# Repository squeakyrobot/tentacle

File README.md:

# tentacle
Modular robotic tentacle

TODO: On the project webpage add a simple calculator to help with the tentacle setup that allows the user to
easily configure their tentacle. Also add the maths in this document

## BOM

 * Internal Bearings - [F683ZZ](https://www.amazon.com/gp/product/B07Z3DRZX9)
 * Pulley Bearings - [6700-2RS](https://www.amazon.com/gp/product/B082PR3DFZ)

## Motor Options

## 28BYJ-48
I modified these motors to be bipolar, See [this article](https://ardufocus.com/howto/28byj-48-bipolar-hw-mod/)

## TODO:

- Add NEMA-11 support
- Add NEMA-14 support
- Test different configurations
    - Spine size
        - 4mm OD, 3mm ID
        - 4mm OD, 2mm ID
        - 6mm OD, 3mm ID
    - Cable materials

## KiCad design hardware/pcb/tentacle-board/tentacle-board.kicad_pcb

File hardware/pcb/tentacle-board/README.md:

# Tentacle Controller PCB

TODO: Add more details about the board

## Pinout

Both motors share microstep configuration pins and the enable pin.

### Microstep Configuration

| **DRV8825 Pin** 	| **RP2040 Pin** 	|
|-----------------	|----------------	|
| MODE 0           	| GPIO3          	|
| MODE 1           	| GPIO2          	|
| MODE 2          	| GPIO1          	|

### Motor A

| **DRV8825 Pin** 	| **RP2040 Pin** 	|
|-----------------	|----------------	|
| DIR             	| GPIO6          	|
| STEP            	| GPIO4          	|
| ENABLE          	| GPIO5          	|
| SLEEP           	| GPIO8          	|
| RESET           	| GPIO9          	|
| HOME            	| GPIO0          	|
| FAULT           	| GPIO7          	|

### Motor B

| **DRV8825 Pin** 	| **RP2040 Pin** 	|
|-----------------	|----------------	|
| DIR             	| GPIO12          	|
| STEP            	| GPIO11          	|
| ENABLE          	| GPIO5          	|
| SLEEP           	| GPIO14          	|
| RESET           	| GPIO15          	|
| HOME            	| GPIO10          	|
| FAULT           	| GPIO13          	|

### Debug Connector

| **Connector Pin** | **RP2040 Pin** |
|-----------------	|----------------|
| 1             	| SWCLK          |
| 2            	    | GND          	 |
| 3           	    | SWD          	 |

### UART Connector

| **Connector Pin** | **RP2040 Pin**    | **Pin Functions** |
|-----------------	|----------------   |----------------   |
| 1             	| GPIO17            | UART0 RX          |
| 2            	    | GND          	    |                   |
| 3           	    | GPIO16            | UART0 TX          |

### CTRL Connector

| **Connector Pin** | **RP2040 Pin**    | **Pin Functions**     |
|-----------------	|----------------   |----------------       |
| 1             	| GND               |                       |
| 2            	    | RUN      	        | Reset when driven low |
| 3           	    | GPIO19            |                       |
| 4           	    | GPIO20            | UART1 TX, I2C0 SDA    |
| 5           	    | GPIO21            | UART1 RX, I2C0 SCL    |

### AUX1 Connector

| **Connector Pin** | **RP2040 Pin**    | **Pin Functions**     |
|-----------------	|----------------   |----------------       |
| 1             	| GND               |                       |
| 2            	    | GPIO22      	    |                       |
| 3           	    | GPIO23            |                       |
| 4           	    | GPIO24            |                       |
| 5           	    | GPIO25            |                       |

### AUX2 Connector

| **Connector Pin** | **RP2040 Pin**    | **Pin Functions**     |
|-----------------	|----------------   |----------------       |
| 1             	| GND               |                       |
| 2            	    | GPIO26      	    | ADC0                  |
| 3           	    | GPIO27            | ADC1                  |
| 4           	    | GPIO28            | ADC2                  |
| 5           	    | GPIO29            | ADC3                  |

### Motor Connectors

All motor connectors map to the same pins of their corresponding DRV8825 modules 

| **Connector Pin** | **DRV8825 Pin**   |
|-----------------	|----------------	|
| 1             	| B2          	    |
| 2            	    | B1          	    |
| 3          	    | A1          	    |
| 4           	    | A2          	    |

## Revision History

### v1.0

 * Initial Release

### v1.1

 * **NOT COMPLETE**
 * Fix issue with missing silkscreen items

## TODO:

 * Investigate alternative motor connectors
    - Change to JST-PH 2mm
 * Investigate alternative power connector
 * Switch interface connectors to right angle
 * Switch to a shared SLEEP and individual ENABLE
 * Add software configurable VREF, perhaps have the pot be the max
 * Make CTRL & AUX connectors 90 degrees

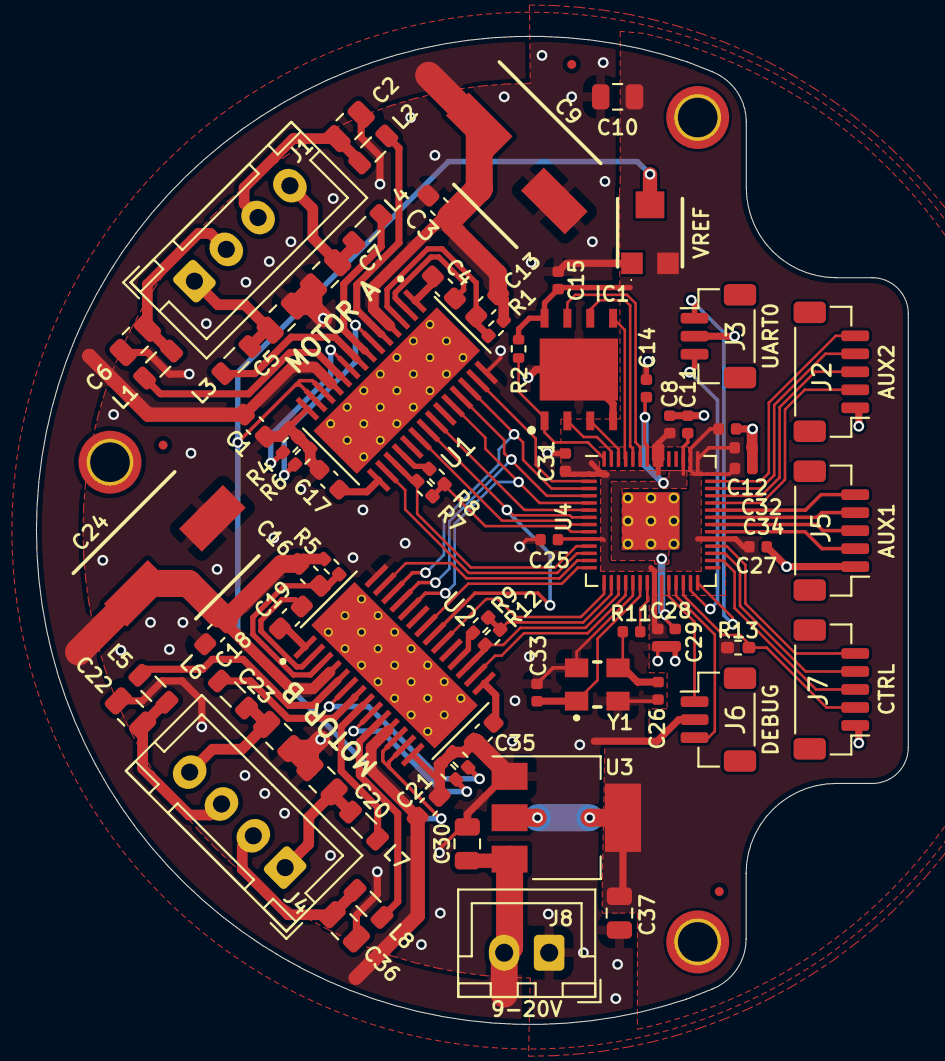
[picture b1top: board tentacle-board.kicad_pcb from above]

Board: 2 copper layers, 48.4 x 54.9 mm, 79 parts (0 on the bottom side), 76 nets.

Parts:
C1, C3, C13, C16, C18, C21: 0.1uf; C_0603_1608Metric_Pad1.08x0.95mm_HandSolder
C2, C5, C6, C7, C20, C22, C23, C36: 1nF; C_0805_2012Metric
C4, C19: 10nF; C_0603_1608Metric_Pad1.08x0.95mm_HandSolder
C8, C14, C15, C25, C27, C28, C29, C31, C32, C34: 100nF; C_0402_1005Metric
C9, C24: 100uF; CAPAE660X800N
C10, C30, C37: 10uF; C_0805_2012Metric
C11, C12: 1uF; C_0402_1005Metric
C17, C35: 0.47uF; C_0603_1608Metric
C26, C33: 30pF; C_0402_1005Metric
FID1, FID2, FID3: Fiducial; Fiducial_0.5mm_Mask1mm
H1, H2, H3: MountingHole; MountingHole_2.2mm_M2_ISO7380_Pad_TopBottom
IC1: W25Q32JVZPIQ; SON127P600X500X80-9N-D
J1, J4: Motor; JST_XH_B4B-XH-A_1x04_P2.50mm_Vertical
J2: AUX2; JST_SH_BM05B-SRSS-TB_1x05-1MP_P1.00mm_Vertical
J3: UART0; JST_SH_BM03B-SRSS-TB_1x03-1MP_P1.00mm_Vertical
J5: AUX1; JST_SH_BM05B-SRSS-TB_1x05-1MP_P1.00mm_Vertical
J6: DEBUG; JST_SH_BM03B-SRSS-TB_1x03-1MP_P1.00mm_Vertical
J7: CTRL; JST_SH_BM05B-SRSS-TB_1x05-1MP_P1.00mm_Vertical
J8: Conn_01x02; JST_XH_B2B-XH-A_1x02_P2.50mm_Vertical
L1, L2, L3, L4, L5, L6, L7, L8: L_Ferrite; L_0805_2012Metric
R1, R5: 1M; R_0402_1005Metric_Pad0.72x0.64mm_HandSolder
R2: 10k; R_0402_1005Metric
R3, R4, R6, R10: 0.1; R_0402_1005Metric_Pad0.72x0.64mm_HandSolder
R7, R12: 10k; R_0402_1005Metric_Pad0.72x0.64mm_HandSolder
R8, R9, R13: 1.5k; R_0402_1005Metric_Pad0.72x0.64mm_HandSolder
R11: 1k; C_0402_1005Metric
U1, U2: DRV8825PWP; IC_TPS61196PWPRQ1
U3: NCP1117-3.3_SOT223; SOT-223-3_TabPin2
U4: RP2040; RP2040-QFN-56
VR1: TC33X-2-103E; TC33X2503E
Y1: ABM8-12.000MHZ-20-B1U-T; ABM810000MHZ12D2W

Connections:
+1V1: C11.1, C14.1, C29.1, U4.23 (DVDD), U4.45 (VREG_VOUT), U4.50 (DVDD)
+3V3: C8.1, C10.1, C12.1, C15.1, C25.1, C27.1, C28.1, C31.1, C32.1, C34.1, C37.1, IC1.8 (VCC), R2.1, R13.2, U3.2 (VO), U4.1 (IOVDD), U4.10 (IOVDD), U4.22 (IOVDD), U4.33 (IOVDD), U4.42 (IOVDD), U4.43 (ADC_AVDD), U4.44 (VREG_IN), U4.48 (USB_VDD), U4.49 (IOVDD), VR1.3 (CW)
/GPIO0: U1.27 (NHOME), U4.2 (GPIO0)
/GPIO1: U1.26 (MODE2), U2.26 (MODE2), U4.3 (GPIO1)
/GPIO2: U1.25 (MODE1), U2.25 (MODE1), U4.4 (GPIO2)
/GPIO3: U1.24 (MODE0), U2.24 (MODE0), U4.5 (GPIO3)
/GPIO4: U1.22 (STEP), U4.6 (GPIO4)
/GPIO5: U1.21 (NENBL), U2.21 (NENBL), U4.7 (GPIO5)
/GPIO6: U1.20 (DIR), U4.8 (GPIO6)
/GPIO7: R7.1, R8.2, U4.9 (GPIO7)
/GPIO8: R7.2, U1.17 (NSLEEP), U4.11 (GPIO8)
/GPIO9: U1.16 (~NRESET), U4.12 (GPIO9)
/GPIO10: U2.27 (NHOME), U4.13 (GPIO10)
/GPIO11: U2.22 (STEP), U4.14 (GPIO11)
/GPIO12: U2.20 (DIR), U4.15 (GPIO12)
/GPIO13: R9.2, R12.1, U4.16 (GPIO13)
/GPIO14: R12.2, U2.17 (NSLEEP), U4.17 (GPIO14)
/GPIO15: U2.16 (~NRESET), U4.18 (GPIO15)
/GPIO16: J3.3, U4.27 (GPIO16)
/GPIO17: J3.1, U4.28 (GPIO17)
/GPIO19: J7.3, U4.30 (GPIO19)
/GPIO20: J7.4, U4.31 (GPIO20)
/GPIO21: J7.5, U4.32 (GPIO21)
/GPIO22: J5.2, U4.34 (GPIO22)
/GPIO23: J5.3, U4.35 (GPIO23)
/GPIO24: J5.4, U4.36 (GPIO24)
/GPIO25: J5.5, U4.37 (GPIO25)
/GPIO26_ADC0: J2.2, U4.38 (GPIO26_ADC0)
/GPIO27_ADC1: J2.3, U4.39 (GPIO27_ADC1)
/GPIO28_ADC2: J2.4, U4.40 (GPIO28_ADC2)
/GPIO29_ADC3: J2.5, U4.41 (GPIO29_ADC3)
/Motor Driver A/A1: C2.1, J1.3, L2.2
/Motor Driver A/A2: C7.1, J1.4, L4.2
/Motor Driver A/B1: C6.1, J1.2, L1.2
/Motor Driver A/B2: C5.1, J1.1, L3.2
/Motor Driver A/VREF: U1.12 (AVREF), U1.13 (BVREF), U2.12 (AVREF), U2.13 (BVREF), VR1.2 (WIPER)
/Motor Driver B/A1: C22.1, J4.3, L5.2
/Motor Driver B/A2: C23.1, J4.4, L6.2
/Motor Driver B/B1: C36.1, J4.2, L8.2
/Motor Driver B/B2: C20.1, J4.1, L7.2
/QSPI_SCLK: IC1.6 (CLK), U4.52 (QSPI_SCLK)
/QSPI_SD0: IC1.5 (DI_(IO0)), U4.53 (QSPI_SD0)
/QSPI_SD1: IC1.2 (DO_(IO1)), U4.55 (QSPI_SD1)
/QSPI_SD2: IC1.3 (~WP_(IO2)), U4.54 (QSPI_SD2)
/QSPI_SD3: IC1.7 (~RESET_(IO3)), U4.51 (QSPI_SD3)
/QSPI_SS: IC1.1 (~CS), R2.2, U4.56 (QSPI_SS)
/RUN: J7.2, R13.1, U4.26 (RUN)
/SWCLK: J6.1, U4.24 (SWCLK)
/SWD: J6.3, U4.25 (SWD)
/XIN: C33.1, U4.20 (XIN), Y1.1 (X1)
/XOUT: R11.1, U4.21 (XOUT)
GND: C1.2, C2.2, C3.2, C5.2, C6.2, C7.2, C8.2, C9.2, C10.2, C11.2, C12.2, C14.2, C15.2, C17.2, C18.2, C20.2, C21.2, C22.2, C23.2, C24.2, C25.2, C26.2, C27.2, C28.2, C29.2, C30.2, C31.2, C32.2, C33.2, C34.2, C35.2, C36.2, C37.2, IC1.4 (GND), IC1.9 (EP), J2.1, J3.2, J5.1, J6.2, J7.1, J8.1, R3.2, R4.2, R6.2, R10.2, U1.14 (GND), U1.28 (GND__1), U2.14 (GND), U2.28 (GND__1), U3.1 (GND), U4.19 (TESTEN), U4.57 (GND), VR1.1 (CCW), Y1.2 (GND_1), Y1.4 (GND_2)
unnamed: L2.1, U1.5 (AOUT1)
unnamed: L4.1, U1.7 (AOUT2)
unnamed: L1.1, U1.10 (BOUT1)
unnamed: L3.1, U1.8 (BOUT2)
unnamed: C4.1, U1.1 (CP1)
unnamed: C4.2, U1.2 (CP2)
unnamed: R6.1, U1.6 (ISENA)
unnamed: R4.1, U1.9 (ISENB)
unnamed: R8.1, U1.18 (NFAULT)
unnamed: C17.1, U1.15 (V3P3OUT)
unnamed: C13.1, R1.2, U1.3 (VCP)
unnamed: L5.1, U2.5 (AOUT1)
unnamed: L6.1, U2.7 (AOUT2)
unnamed: L8.1, U2.10 (BOUT1)
unnamed: L7.1, U2.8 (BOUT2)
unnamed: C19.1, U2.1 (CP1)
unnamed: C19.2, U2.2 (CP2)
unnamed: R10.1, U2.6 (ISENA)
unnamed: R3.1, U2.9 (ISENB)
unnamed: R9.1, U2.18 (NFAULT)
unnamed: C35.1, U2.15 (V3P3OUT)
unnamed: C16.1, R5.2, U2.3 (VCP)
unnamed: C26.1, R11.2, Y1.3 (X2)
VDC: C1.1, C3.1, C9.1, C13.2, C16.2, C18.1, C21.1, C24.1, C30.1, J8.2, R1.1, R5.1, U1.4 (VMA), U1.11 (VMB), U2.4 (VMA), U2.11 (VMB), U3.3 (VI)

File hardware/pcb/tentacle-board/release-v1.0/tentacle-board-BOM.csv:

Id,Designator,Footprint,Quantity,Designation,LCSC Part Number
1,"C37,C30,C10",C_0805_2012Metric,3,10uF,C15850
2,"C12,C11",C_0402_1005Metric,2,1uF,C107372
3,"C25,C15,C8,C27,C28,C29,C31,C32,C14,C34",C_0402_1005Metric,10,100nF,C60474
4,U3,SOT-223-3_TabPin2,1,NCP1117-3.3_SOT223,C2902118
5,"C26,C33",C_0402_1005Metric,2,30pF,C107004
6,U4,RP2040-QFN-56,1,RP2040,C2040
7,R11,C_0402_1005Metric,1,1k,C11702
8,Y1,ABM810000MHZ12D2W,1,ABM8-12.000MHZ-20-B1U-T,C133334
9,VR1,TC33X2503E,1,TC33X-2-103E,C719176
10,"J7,J2,J5",JST_SH_BM05B-SRSS-TB_1x05-1MP_P1.00mm_Vertical,1,JST_SH_BM05B,C160391
11,"L7,L6,L2,L8,L5,L1,L3,L4",L_0805_2012Metric,8,L_Ferrite,C369519
12,"R6,R3,R4,R10",R_0402_1005Metric_Pad0.72x0.64mm_HandSolder,4,0.1ohms,C3013344
13,"R5,R1",R_0402_1005Metric_Pad0.72x0.64mm_HandSolder,2,1M,C138033
14,"C20,C2,C22,C23,C5,C6,C36,C7",C_0805_2012Metric,8,1nF,C51210
15,"C35,C17",C_0603_1608Metric,2,0.47uF,C577418
17,"J4,J1",JST_XH_B4B-XH-A_1x04_P2.50mm_Vertical,2,Motor,C37815
18,"J6,J3",JST_SH_BM03B-SRSS-TB_1x03-1MP_P1.00mm_Vertical,1,BM03B-SRSS,C160389
19,"C4,C19",C_0603_1608Metric_Pad1.08x0.95mm_HandSolder,2,10nF,C100042
20,"C3,C16,C1,C18,C21,C13",C_0603_1608Metric_Pad1.08x0.95mm_HandSolder,6,0.1uf,C3011705
21,"R12,R7,R2",R_0402,2,10k,C60490
23,"C9,C24",CAPAE660X800N,2,100uF,C250945
24,"U1,U2",IC_TPS61196PWPRQ1,2,DRV8825PWP,C81582
25,IC1,SON127P600X500X80-9N-D,1,W25Q32JVZPIQ,C571260
26,"R9,R8,R13",R_0402_1005Metric_Pad0.72x0.64mm_HandSolder,3,1.5k,C114759
29,J8,JST_XH_B2B-XH-A_1x02_P2.50mm_Vertical,1,Power,C442299

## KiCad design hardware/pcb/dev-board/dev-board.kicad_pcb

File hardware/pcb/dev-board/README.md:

# Development Board

TODO: Add more details about the board

## Pinout

### Microstep Configuration

Both motors share microstep configuration pins

| **DRV8825 Pin** 	| **Pico Pin** 	|
|-----------------	|----------------	|
| MODE 0           	| GPIO2          	|
| MODE 1           	| GPIO3          	|
| MODE 2          	| GPIO4          	|

### Motor 1

| **DRV8825 Pin** 	| **Pico Pin** 	    |
|-----------------	|----------------   |
| DIR             	| GPIO7          	|
| STEP            	| GPIO6          	|
| ENABLE          	| GND          	    |
| SLEEP           	| GPIO8          	|
| RESET           	| GND          	    |
| FAULT           	| GND          	    |

### Motor 2

| **DRV8825 Pin** 	| **Pico Pin** 	    |
|-----------------	|----------------   |
| DIR             	| GPIO10          	|
| STEP            	| GPIO9          	|
| ENABLE          	| GND          	    |
| SLEEP           	| GPIO8          	|
| RESET           	| GND          	    |
| FAULT           	| GND          	    |

### Motor 3

| **DRV8825 Pin** 	| **Pico Pin** 	    |
|-----------------	|----------------   |
| DIR             	| GPIO13          	|
| STEP            	| GPIO12          	|
| ENABLE          	| GND          	    |
| SLEEP           	| GPIO11          	|
| RESET           	| GND          	    |
| FAULT           	| GND          	    |

### Motor 4

| **DRV8825 Pin** 	| **Pico Pin** 	    |
|-----------------	|----------------   |
| DIR             	| GPIO16          	|
| STEP            	| GPIO15          	|
| ENABLE          	| GND          	    |
| SLEEP           	| GPIO14          	|
| RESET           	| GND          	    |
| FAULT           	| GND          	    |

### Motor Connectors

All motor connectors map to the same pins of their corresponding DRV8825 modules 

| **Connector Pin** | **DRV8825 Pin**   |
|-----------------	|----------------	|
| 1             	| B2          	    |
| 2            	    | B1          	    |
| 3          	    | A1          	    |
| 4           	    | A2          	    |

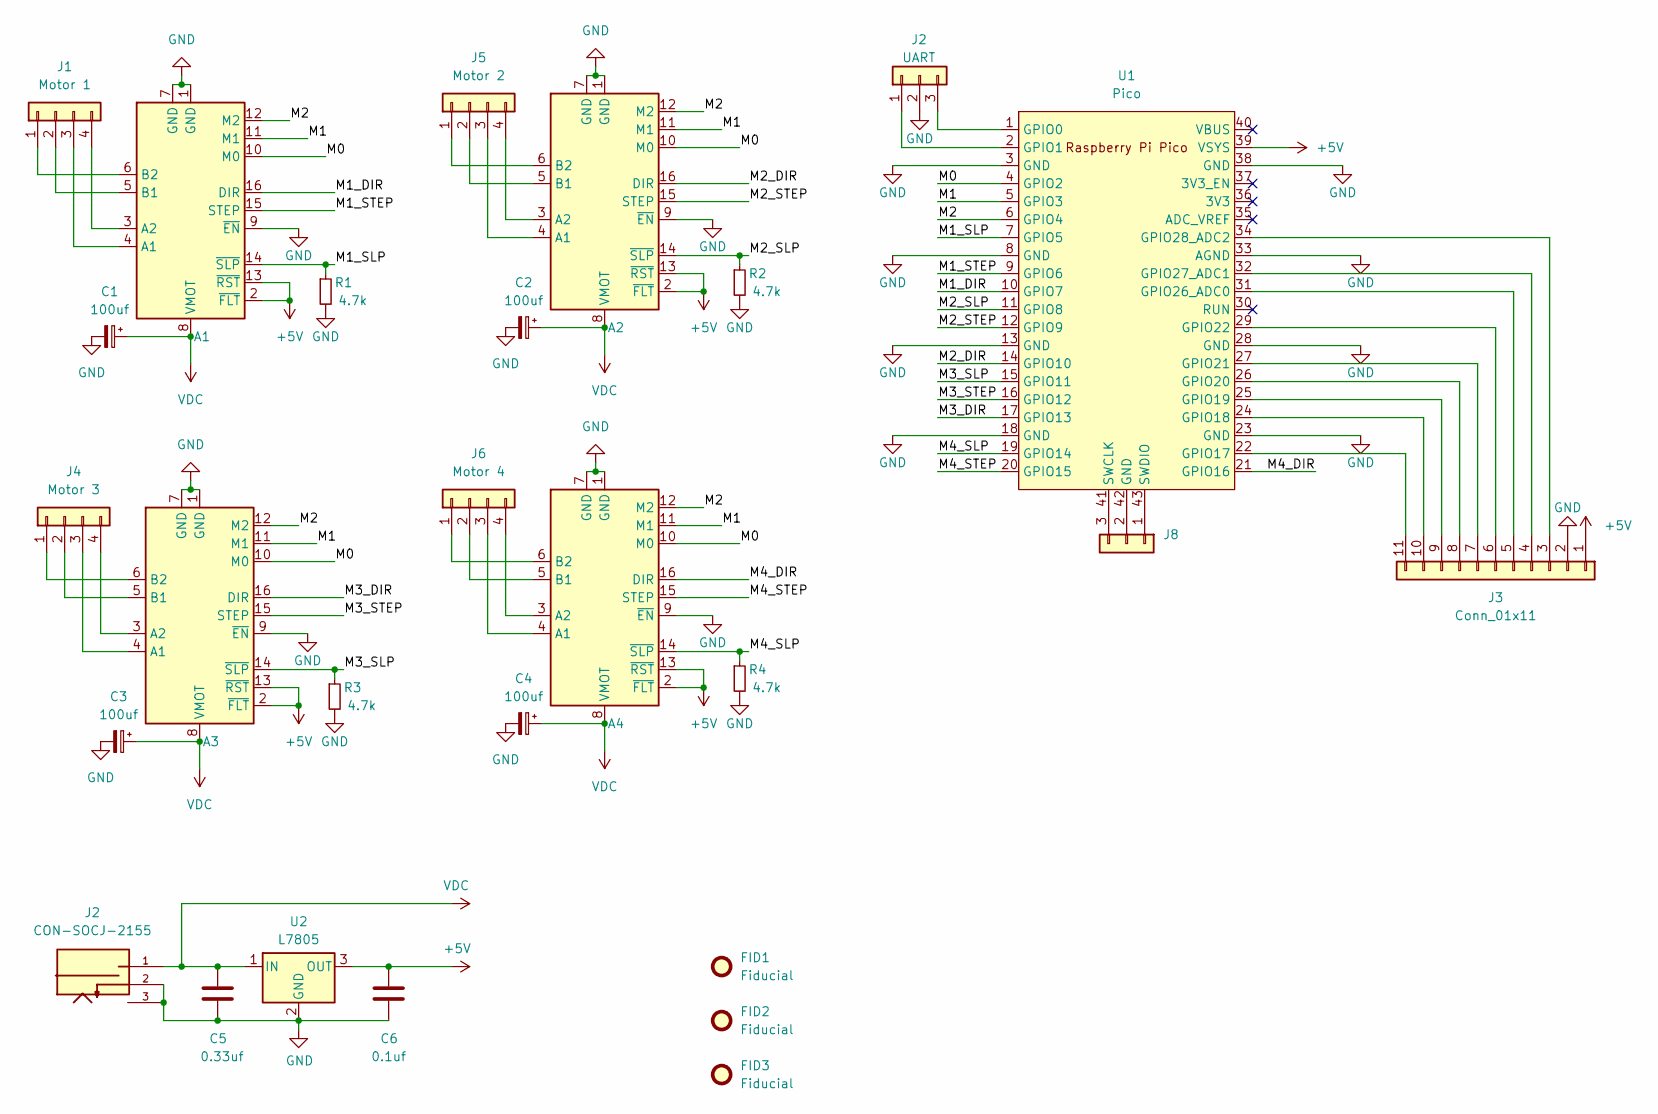
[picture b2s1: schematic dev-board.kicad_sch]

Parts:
A1, A2, A3, A4: Pololu_Breakout_DRV8825; Pololu_Breakout-16_15.2x20.3mm
C1, C2, C3, C4: 100uf; CP_Radial_D6.3mm_P2.50mm
C5: 0.33uf; C_0805_2012Metric_Pad1.18x1.45mm_HandSolder; Mfg # C0805C224K1RACTU; Mouser # 80-C0805C224K1R
C6: 0.1uf; C_0805_2012Metric_Pad1.18x1.45mm_HandSolder; Mfr # KGM21NR71H104KT; Mouser # 581-KGM21NR71H104KT
FID1, FID2, FID3: Fiducial; Fiducial_1mm_Mask2mm
J1: Motor 1; JST_XH_B4B-XH-A_1x04_P2.50mm_Vertical
J2: CON-SOCJ-2155; GRAVITECH_CON-SOCJ-2155; PARTREV NA
J3: Conn_01x11; PinHeader_1x11_P2.54mm_Vertical
J4: Motor 3; JST_XH_B4B-XH-A_1x04_P2.50mm_Vertical
J5: Motor 2; JST_XH_B4B-XH-A_1x04_P2.50mm_Vertical
J6: Motor 4; JST_XH_B4B-XH-A_1x04_P2.50mm_Vertical
J8: Conn_01x03; JST_XH_B3B-XH-A_1x03_P2.50mm_Vertical
R1, R2, R3, R4: 4.7k; R_0805_2012Metric_Pad1.20x1.40mm_HandSolder; Mfg # ERJ-HP6D4701V; Mouser # 667-ERJ-HP6D4701V
U1: Pico; RPi_Pico_SMD_TH
U2: L7805; TO-220-3_Vertical; Mfg # LM7805CT/NOPB

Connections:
+5V: A1.2 (~FLT), A1.13 (~RST), A2.2 (~FLT), A2.13 (~RST), A3.2 (~FLT), A3.13 (~RST), A4.2 (~FLT), A4.13 (~RST), C6.1, J3.1, U1.39 (VSYS), U2.3 (OUT)
/M0: A1.10 (M0), A2.10 (M0), A3.10 (M0), A4.10 (M0), U1.4 (GPIO2)
/M1: A1.11 (M1), A2.11 (M1), A3.11 (M1), A4.11 (M1), U1.5 (GPIO3)
/M1_DIR: A1.16 (DIR), U1.10 (GPIO7)
/M1_SLP: A1.14 (~SLP), R1.1, U1.7 (GPIO5)
/M1_STEP: A1.15 (STEP), U1.9 (GPIO6)
/M2: A1.12 (M2), A2.12 (M2), A3.12 (M2), A4.12 (M2), U1.6 (GPIO4)
/M2_DIR: A2.16 (DIR), U1.14 (GPIO10)
/M2_SLP: A2.14 (~SLP), R2.1, U1.11 (GPIO8)
/M2_STEP: A2.15 (STEP), U1.12 (GPIO9)
/M3_DIR: A3.16 (DIR), U1.17 (GPIO13)
/M3_SLP: A3.14 (~SLP), R3.1, U1.15 (GPIO11)
/M3_STEP: A3.15 (STEP), U1.16 (GPIO12)
/M4_DIR: A4.16 (DIR), U1.21 (GPIO16)
/M4_SLP: A4.14 (~SLP), R4.1, U1.19 (GPIO14)
/M4_STEP: A4.15 (STEP), U1.20 (GPIO15)
unnamed: A1.4 (A1), J1.3
unnamed: A1.3 (A2), J1.4
unnamed: A1.5 (B1), J1.2
unnamed: A1.6 (B2), J1.1
unnamed: A2.4 (A1), J5.3
unnamed: A2.3 (A2), J5.4
unnamed: A2.5 (B1), J5.2
unnamed: A2.6 (B2), J5.1
unnamed: A3.4 (A1), J4.3
unnamed: A3.3 (A2), J4.4
unnamed: A3.5 (B1), J4.2
unnamed: A3.6 (B2), J4.1
unnamed: A4.4 (A1), J6.3
unnamed: A4.3 (A2), J6.4
unnamed: A4.5 (B1), J6.2
unnamed: A4.6 (B2), J6.1
unnamed: J3.3, U1.34 (GPIO28_ADC2)
unnamed: J3.4, U1.32 (GPIO27_ADC1)
unnamed: J3.5, U1.31 (GPIO26_ADC0)
unnamed: J3.6, U1.29 (GPIO22)
unnamed: J3.7, U1.27 (GPIO21)
unnamed: J3.8, U1.26 (GPIO20)
unnamed: J3.9, U1.25 (GPIO19)
unnamed: J3.10, U1.24 (GPIO18)
unnamed: J3.11, U1.22 (GPIO17)
unnamed: J8.1, U1.43 (SWDIO)
unnamed: J8.2, U1.42 (GND)
unnamed: J8.3, U1.41 (SWCLK)

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
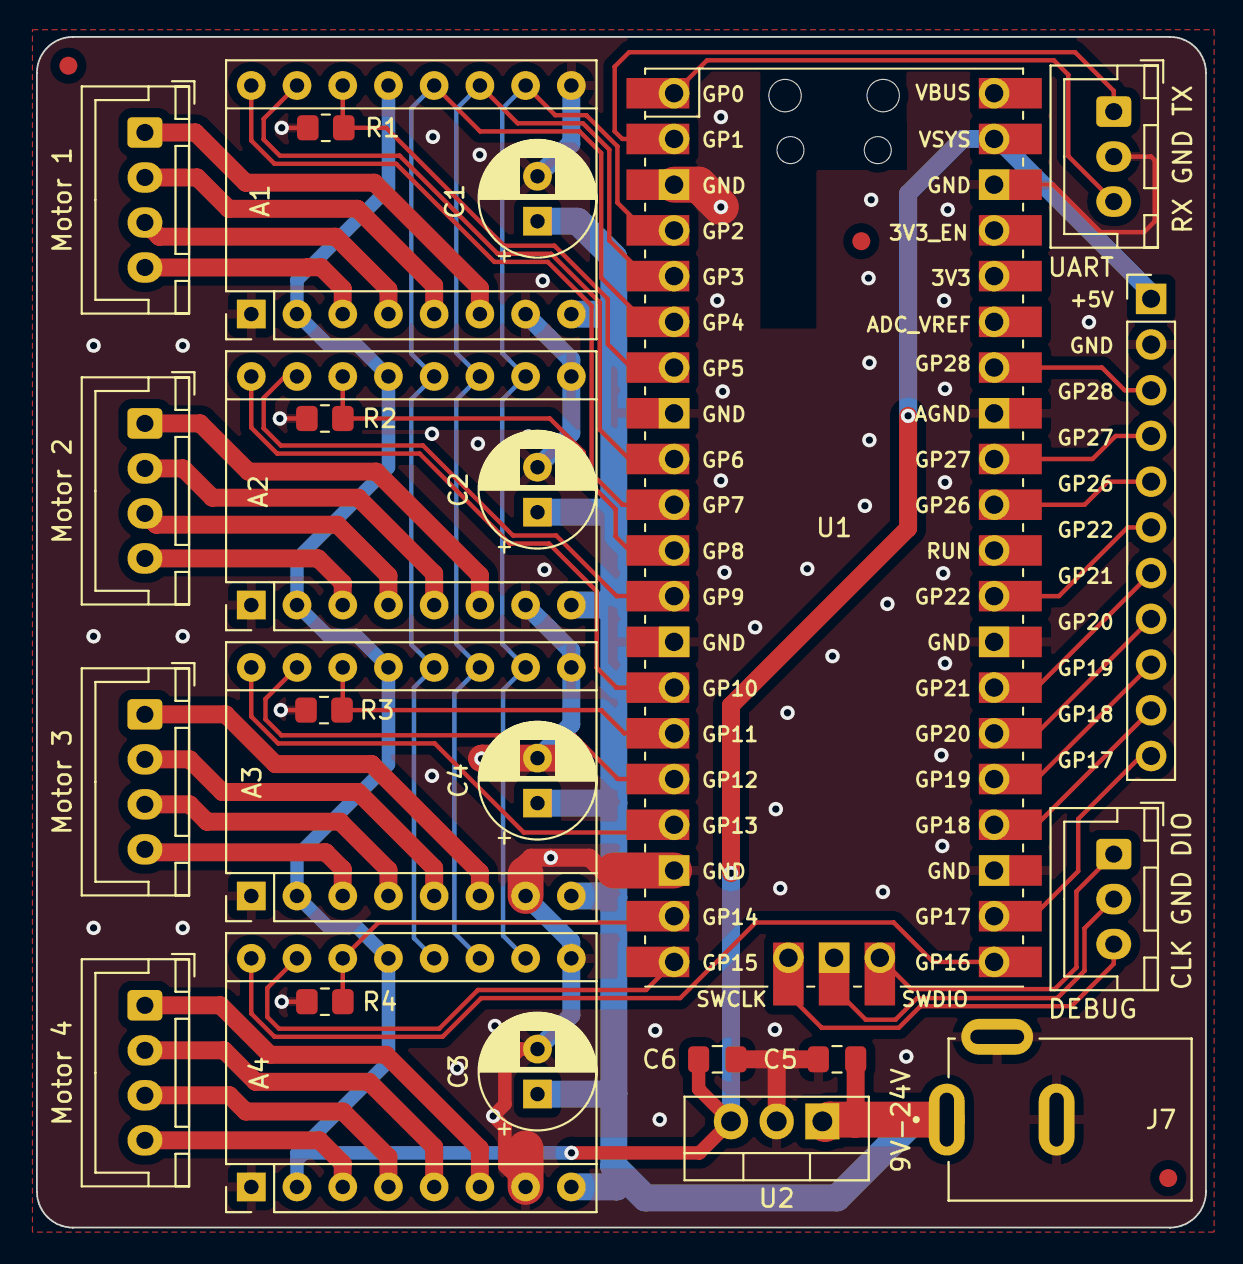
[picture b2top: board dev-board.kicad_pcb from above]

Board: 2 copper layers, 64.9 x 66.2 mm, 27 parts (0 on the bottom side), 48 nets.

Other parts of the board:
J7: CON-SOCJ-2155; GRAVITECH_CON-SOCJ-2155

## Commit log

2023-09-12 Added current stl files, and a project stub for the firmware
2023-09-12 Recreated stub pico project using https://github.com/raspberrypi/pico-project-generator
2023-09-13 Got the basic stepper driver tests done for DRV8830 and TMC2209
2023-09-13 Created the base motor driver interface and a timer based implementation
2023-09-13 Small refactor & reformatting
2023-09-14 Updated to use steps instead of time for stop calculations. Changed config to have maxRPM. Added rotateSteps.
2023-09-14 Moved most of the rotate functionality to the base class
2023-09-14 Added stub for pio driver, no implementation
2023-09-15 Added the interface and stubs for the tentacle controller
2023-09-15 Added gitkeeps to retain directory structure
2023-09-15 Added some, not much, of the tentacle controller implementation
2023-09-16 Added a step counter to the motor driver
2023-09-22 Added bearings to the motor base and did multiple experiments to get it functioning correctly
2023-09-26 Updated CAD & some basic testing
2023-10-13 Updated readme with some todos
2023-10-15 Modified the vertebrae to have a square semi-spherical joint to prevent twiasting and allow for more deterministic positioning
2023-10-17 Added custom PCB to use as a development board
2023-10-17 Finished dev board PCB
2023-10-17 Added stub PCB for the tentacle board based on the RP2049 minimal example
2023-10-18 Added stepper drivers to the tentacle controller PCB
2023-10-19 Worked on the motor power system and stepper driver BOM
2023-10-20 Added the MCU and supporting components and wired them up
2023-10-20 Updated flash to a smaller package, moved in the MCU to make some more room
2023-10-21 Updated references and formatted silkscreen layer
2023-10-23 Added aux plugs and updated the edge cuts
2023-10-24 Finished component & trace layout
2023-10-25 Finished v1 and created manufacturing outputs
2023-10-25 Added some images of the assembled dev-board
2023-11-03 Updated the firmware readme with pinout of the dev board and controller board
2023-11-03 Updated the firmware project to build the custom board. Fixed some missing silkscreen items on the pcb.
2023-11-03 Organized readmes and updated board definition files
2023-11-05 Modified the pulley for printing in a better orientation
2023-11-07 Minor changes from hardware testing
